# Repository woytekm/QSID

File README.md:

Q-SID: a 4-voice polyphonic MIDI synth based on four SID 8580 chips 

Features:

 Hardware/OS: 

 Q-SID will have a modular construction: every functional block of the device will have it's own PCB:
  - CPU board - Raspberry Pi, or other SoC board with two I2C busses, UART, at least 16 GPIO's, USB and ethernet
  - four voice boards, each with one 8580 SID chip
  - MIDI interface board
  - DSP/mixer board 
  - front controls board with rotary encoders and buttons for sound parameters control 
  - front display board 
  - I2C voltage level converter for voice boards
  - power supply with +9V, +5V switched for CPU, +5V linear for voice boards, +3.3V

 Q-SID will have an operating system in form of single multithreaded process of Linux OS, running on custom Raspbian image scaled down to
 stripped Linux kernel, Q-SID OS process, and prefferably nothing more (to spare CPU cycles and other resources).

 Synthetizer features:

  - 4 SID engines with full SID features
  - polyphonic mode with 4 voice polyphony
  - performance mode with keyboard/voice/patch split 
  - arpeggiator (not sure about exact parameters yet)
  - 2 software LFO's modulating filter cutoff/resonance, PWM, oscillator detune, and other parameters
  - onboard sound effects via internal DSP
  - MIDI in/out with programmable MIDI channel
  - embedded .sid chiptune player

====

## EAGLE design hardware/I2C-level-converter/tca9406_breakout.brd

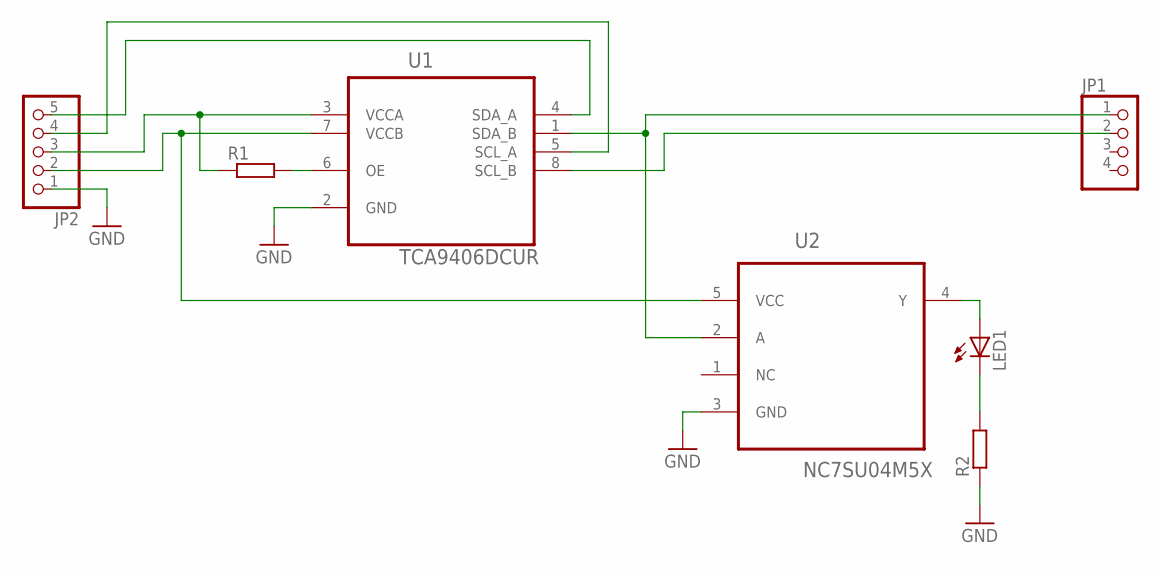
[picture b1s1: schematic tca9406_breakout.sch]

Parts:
JP1: PINHD-1X4; 1X04
JP2: PINHD-1X5; 1X05
LED1: LEDSML1206; SML1206
R1, R2: R-EU_M1406; M1406
U1: TCA9406DCUR; SOP50P310X90-8N
U2: NC7SU04M5X; SOT95P280X145-5N

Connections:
GND: JP2.1, R2.1, U1.2 (GND), U2.3 (GND)
unnamed: JP1.2, U1.8 (SCL_B)
unnamed: JP1.1, U1.1 (SDA_B), U2.2 (A)
unnamed: JP2.5, U1.4 (SDA_A)
unnamed: JP2.4, U1.5 (SCL_A)
unnamed: JP2.3, R1.1, U1.3 (VCCA)
unnamed: JP2.2, U1.7 (VCCB), U2.5 (VCC)
unnamed: LED1.A, U2.4 (Y)
unnamed: R1.2, U1.6 (OE)
unnamed: LED1.C, R2.2

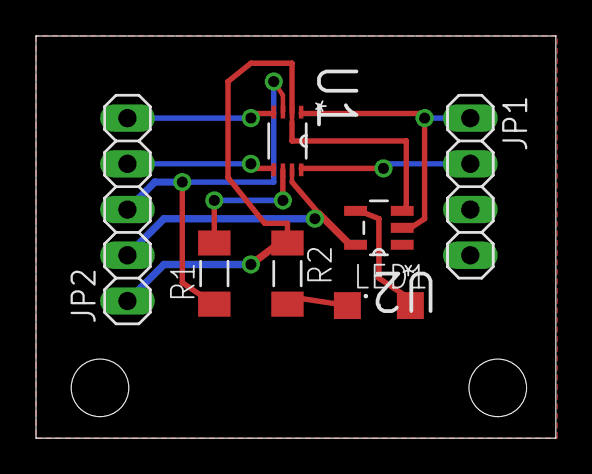
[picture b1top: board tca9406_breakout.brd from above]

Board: 2 copper layers, 28.9 x 22.3 mm, 7 parts (0 on the bottom side), 10 nets.

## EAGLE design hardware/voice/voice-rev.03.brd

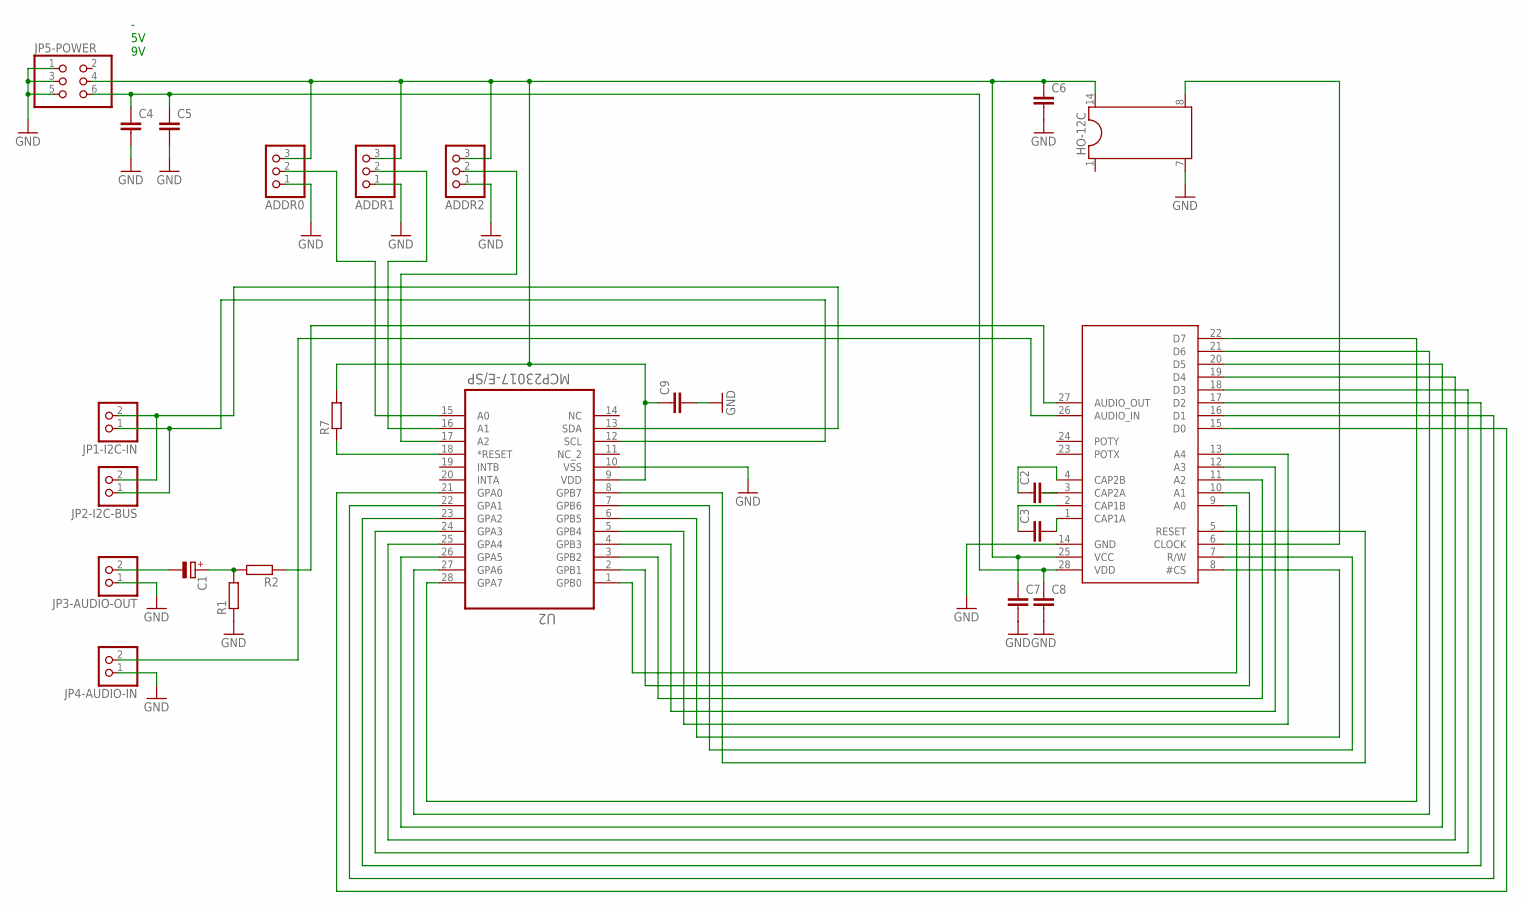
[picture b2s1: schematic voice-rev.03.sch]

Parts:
ADDR0, ADDR1, ADDR2: PINHD-1X3; 1X03
C1: CPOL-EUE2.5-5; E2,5-5
C2, C3: C5/2.5; C5B2.5
C4, C5, C6, C7, C8, C9: C-EU050-024X044; C050-024X044
HO-12C: DIL14/4
JP1-I2C-IN, JP2-I2C-BUS, JP3-AUDIO-OUT, JP4-AUDIO-IN: PINHD-1X2; 1X02
JP5-POWER: PINHD-2X3; 2X03
R1, R2, R7: R-EU_0207/5V; 0207/5V
U2: MCP23017-E/SP; DIP254P762X406-28P
U$1: 6581; DIL28-6

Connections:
GND: ADDR0.1, ADDR1.1, ADDR2.1, C4.2, C5.2, C6.2, C7.2, C8.2, C9.2, HO-12C.7 (8), JP3-AUDIO-OUT.1, JP4-AUDIO-IN.1, JP5-POWER.1, JP5-POWER.3, JP5-POWER.5, R1.1, U2.10 (VSS), U$1.14 (GND)
unnamed: U2.1 (GPB0), U$1.9 (A0)
unnamed: U2.2 (GPB1), U$1.10 (A1)
unnamed: U2.3 (GPB2), U$1.11 (A2)
unnamed: U2.4 (GPB3), U$1.12 (A3)
unnamed: U2.5 (GPB4), U$1.13 (A4)
unnamed: U2.6 (GPB5), U$1.8 (#CS)
unnamed: U2.7 (GPB6), U$1.7 (R/W)
unnamed: U2.8 (GPB7), U$1.5 (RESET)
unnamed: U2.28 (GPA7), U$1.22 (D7)
unnamed: U2.27 (GPA6), U$1.21 (D6)
unnamed: U2.26 (GPA5), U$1.20 (D5)
unnamed: U2.25 (GPA4), U$1.19 (D4)
unnamed: U2.24 (GPA3), U$1.18 (D3)
unnamed: U2.23 (GPA2), U$1.17 (D2)
unnamed: U2.22 (GPA1), U$1.16 (D1)
unnamed: U2.21 (GPA0), U$1.15 (D0)
unnamed: HO-12C.8 (9), U$1.6 (CLOCK)
unnamed: C1.+, R1.2, R2.2
unnamed: C4.1, C5.1, C8.1, JP5-POWER.6, U$1.28 (VDD)
unnamed: R2.1, U$1.27 (AUDIO_OUT)
unnamed: JP4-AUDIO-IN.2, U$1.26 (AUDIO_IN)
unnamed: JP1-I2C-IN.2, JP2-I2C-BUS.2, U2.13 (SDA)
unnamed: JP1-I2C-IN.1, JP2-I2C-BUS.1, U2.12 (SCL)
unnamed: C1.-, JP3-AUDIO-OUT.2
unnamed: C3.2, U$1.1 (CAP1A)
unnamed: C3.1, U$1.2 (CAP1B)
unnamed: C2.2, U$1.3 (CAP2A)
unnamed: C2.1, U$1.4 (CAP2B)
unnamed: ADDR0.2, U2.15 (A0)
unnamed: ADDR1.2, U2.16 (A1)
unnamed: ADDR2.2, U2.17 (A2)
unnamed: R7.1, U2.18 (*RESET)
unnamed: ADDR0.3, ADDR1.3, ADDR2.3, C6.1, C7.1, C9.1, HO-12C.14 (16), JP5-POWER.4, R7.2, U2.9 (VDD), U$1.25 (VCC)

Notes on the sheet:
- 5V 9V

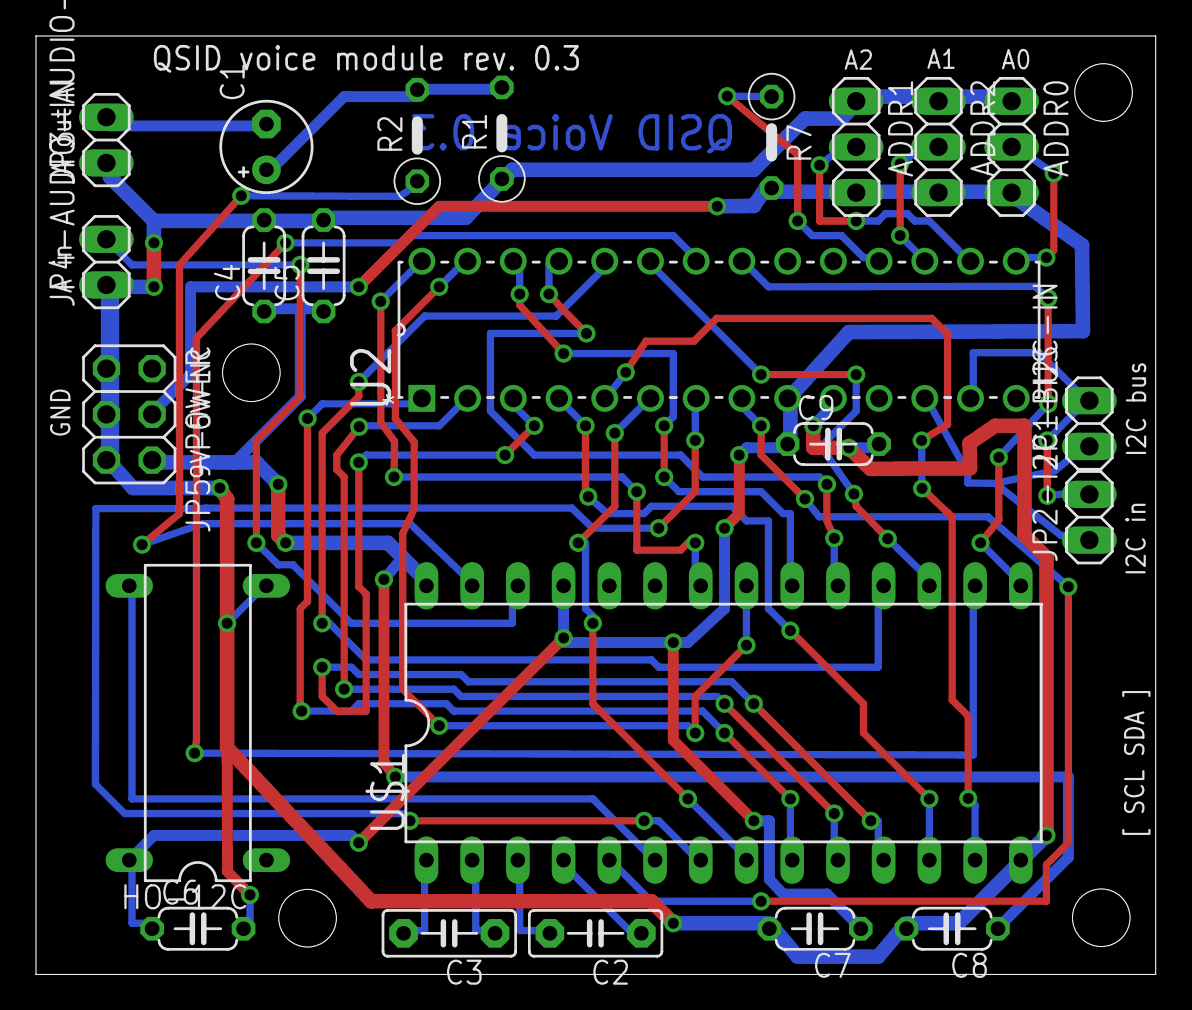
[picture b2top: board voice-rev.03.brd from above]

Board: 2 copper layers, 62.2 x 52.1 mm, 23 parts (0 on the bottom side), 34 nets.

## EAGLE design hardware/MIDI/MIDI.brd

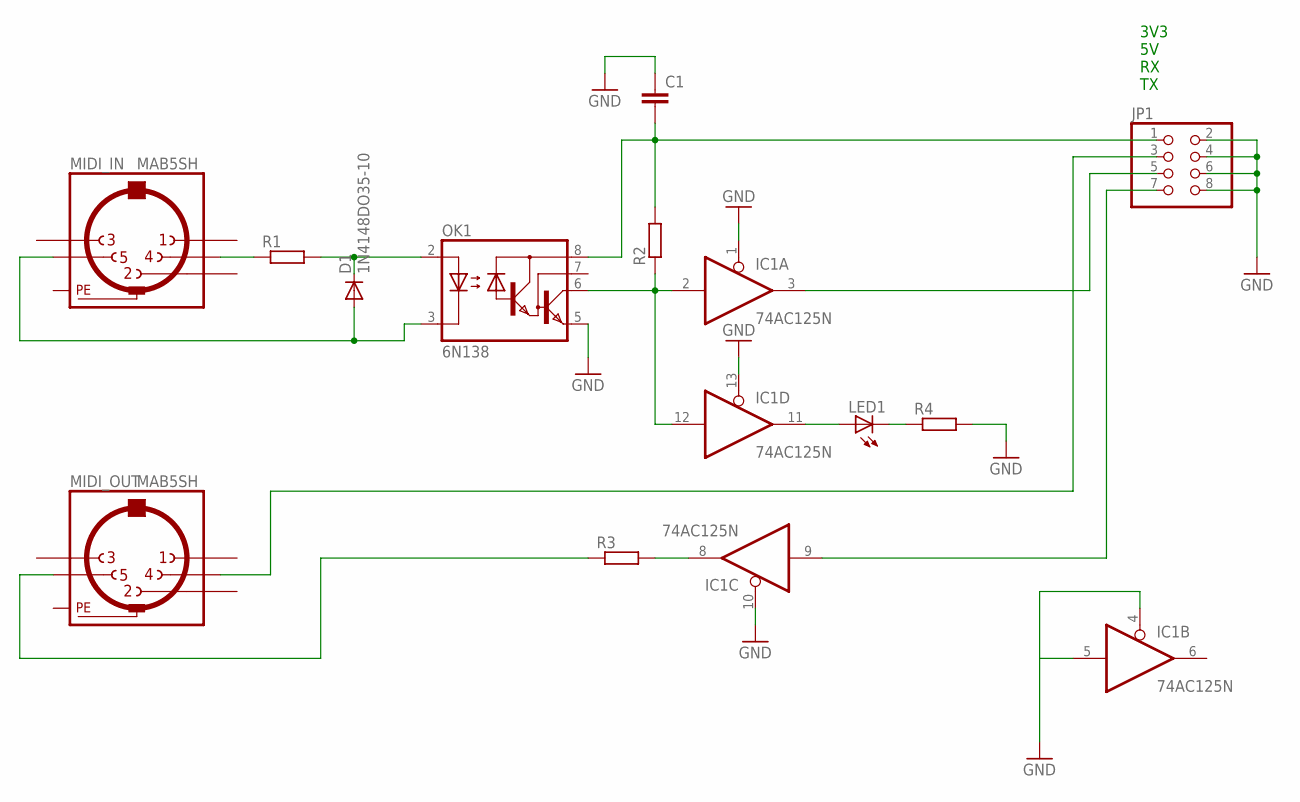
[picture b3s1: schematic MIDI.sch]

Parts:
C1: C-EU050-024X044; C050-024X044
D1: 1N4148DO35-10; DO35-10
IC1: 74AC125N; DIL14
JP1: PINHD-2X4; 2X04
LED1: LED3MM
MIDI_IN: MAB5SH
MIDI_OUT: MAB5SH
OK1: 6N138; DIL08
R1, R2, R3, R4: R-EU_0207/5V; 0207/5V

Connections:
GND: C1.1, IC1.1 (OE), IC1.4 (OE), IC1.5 (I), IC1.7 (GND), IC1.10 (OE), IC1.13 (OE), JP1.2, JP1.4, JP1.6, JP1.8, MIDI_IN.PE, MIDI_IN.PE@ (PE), MIDI_OUT.PE, MIDI_OUT.PE@ (PE), OK1.5 (GND), R4.2
unnamed: MIDI_IN.4, R1.1
unnamed: D1.C, OK1.2 (A), R1.2
unnamed: D1.A, MIDI_IN.5, OK1.3 (C)
unnamed: IC1.8 (O), R3.2
unnamed: IC1.2 (I), IC1.12 (I), OK1.6 (VO), R2.1
unnamed: IC1.3 (O), JP1.5
unnamed: MIDI_OUT.5, R3.1
unnamed: JP1.3, MIDI_OUT.4
unnamed: IC1.9 (I), JP1.7
unnamed: IC1.11 (O), LED1.A
unnamed: LED1.K (C), R4.1
VCC: C1.2, IC1.14 (VCC), JP1.1, OK1.8 (VCC), R2.2

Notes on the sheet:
3V3 5V RX TX

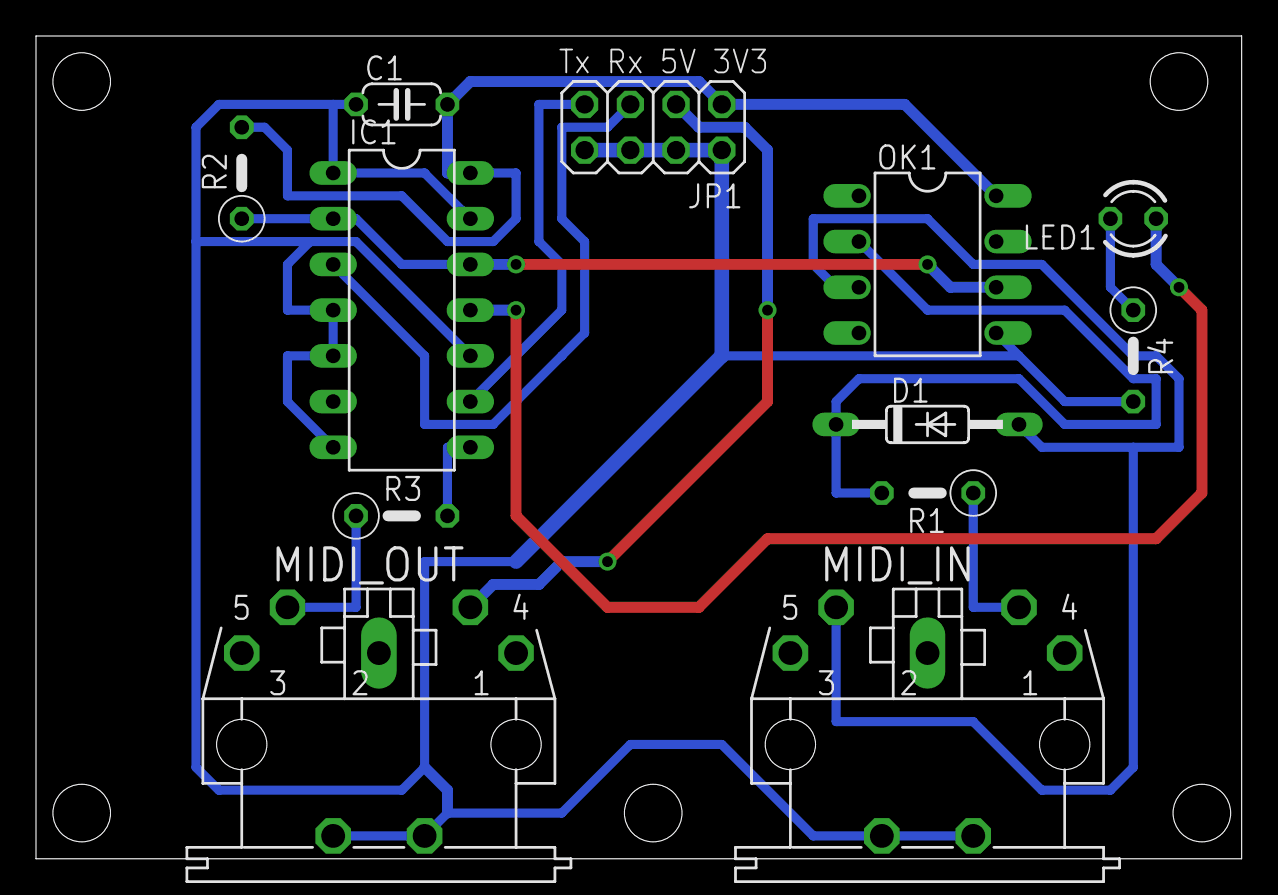
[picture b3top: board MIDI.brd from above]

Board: 2 copper layers, 67.0 x 45.7 mm, 12 parts (0 on the bottom side), 13 nets.

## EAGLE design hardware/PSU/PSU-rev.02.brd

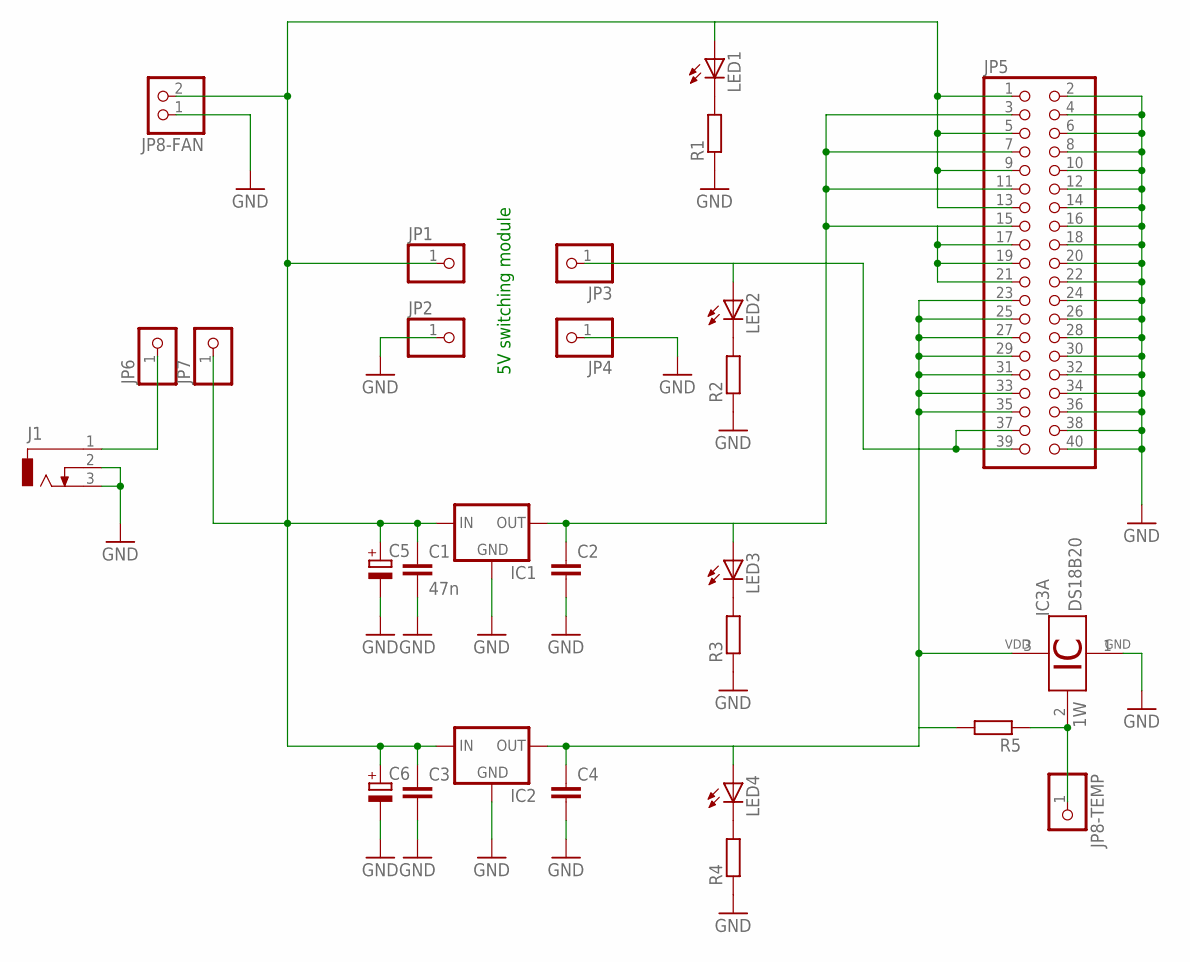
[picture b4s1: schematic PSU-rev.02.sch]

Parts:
C1: 47n; C050-024X044
C2, C3, C4: C-EU050-024X044; C050-024X044
C5, C6: CPOL-EUE3.5-8; E3,5-8
IC1, IC2: 78XXL
IC3: DS18B20; TO92-
J1: DCJ0303
JP1, JP2, JP3, JP4, JP6, JP7, JP8-TEMP: PINHD-1X1; 1X01
JP5: PINHD-2X20; 2X20
JP8-FAN: PINHD-1X2; 1X02
LED1, LED2, LED3, LED4: LEDSML1206; SML1206
R1, R2, R3, R4, R5: R-EU_R1206; R1206

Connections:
GND: C1.2, C2.2, C3.2, C4.2, C5.-, C6.-, IC1.GND, IC2.GND, IC3.1 (GND), J1.2, J1.3, JP2.1, JP4.1, JP5.2, JP5.4, JP5.6, JP5.8, JP5.10, JP5.12, JP5.14, JP5.16, JP5.18, JP5.20, JP5.22, JP5.24, JP5.26, JP5.28, JP5.30, JP5.32, JP5.34, JP5.36, JP5.38, JP5.40, JP8-FAN.1, R1.1, R2.1, R3.1, R4.1
unnamed: C1.1, C3.1, C5.+, C6.+, IC1.IN, IC2.IN, JP1.1, JP5.1, JP5.5, JP5.9, JP5.13, JP7.1, JP8-FAN.2, LED1.A
unnamed: C2.1, IC1.OUT, JP5.3, JP5.7, JP5.11, JP5.15, JP5.17, JP5.19, JP5.21, LED3.A
unnamed: C4.1, IC2.OUT, IC3.3 (VDD), JP5.23, JP5.25, JP5.27, JP5.29, JP5.31, JP5.33, JP5.35, LED4.A, R5.2
unnamed: JP3.1, JP5.37, JP5.39, LED2.A
unnamed: J1.1, JP6.1
unnamed: IC3.2 (1W), JP8-TEMP.1, R5.1
unnamed: LED1.C, R1.2
unnamed: LED2.C, R2.2
unnamed: LED3.C, R3.2
unnamed: LED4.C, R4.2

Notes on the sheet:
5V switching module

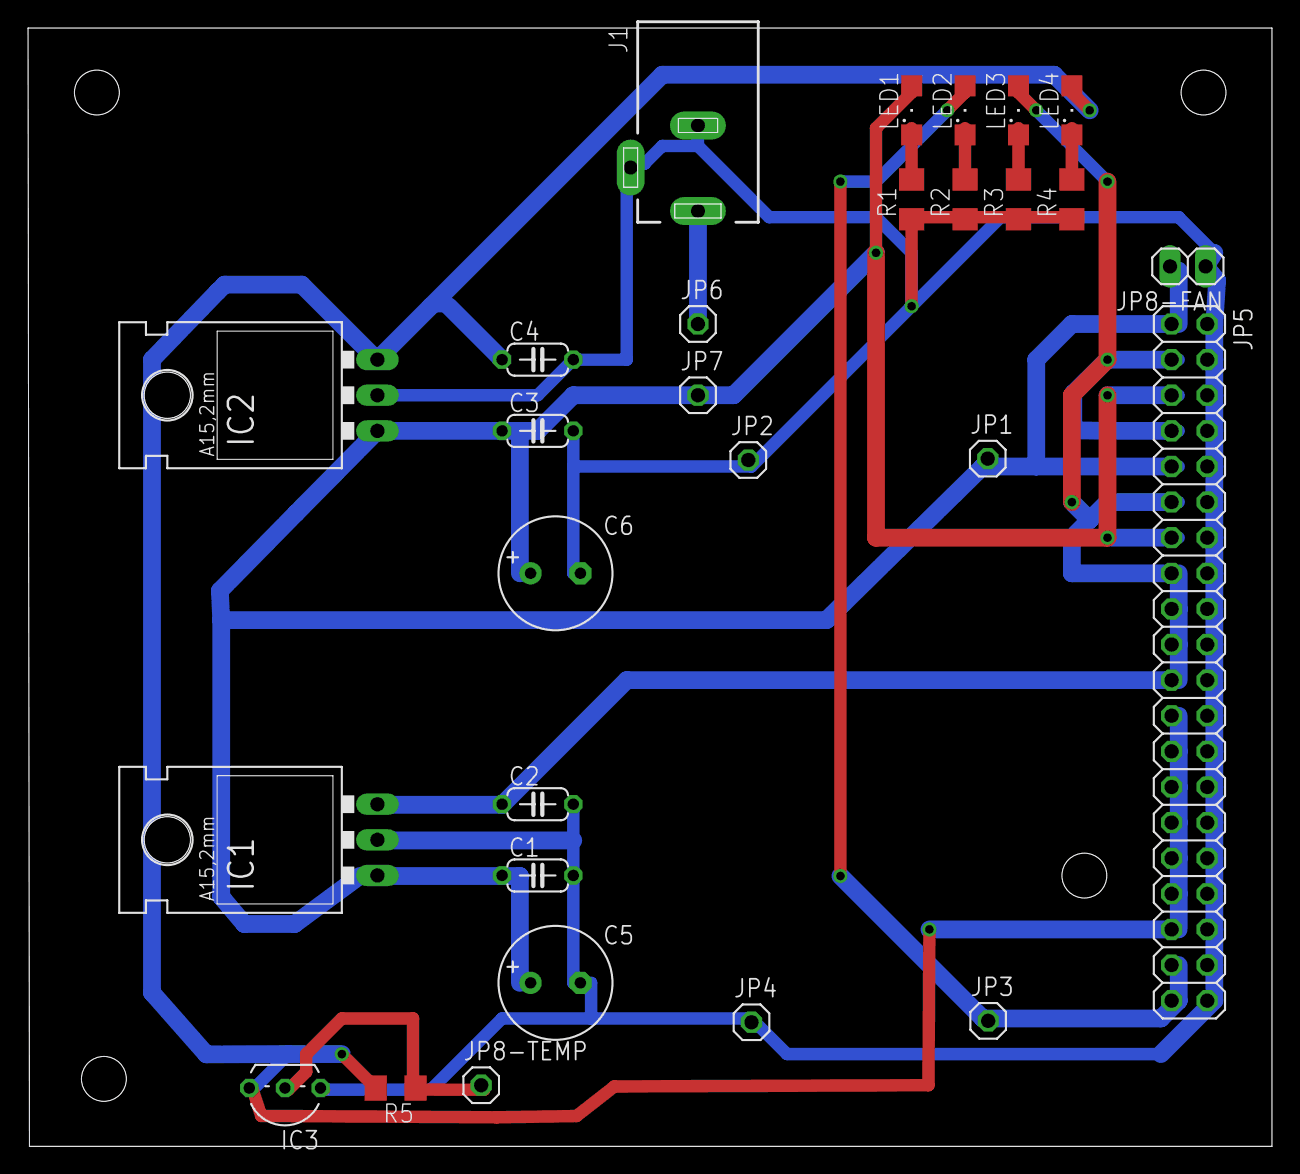
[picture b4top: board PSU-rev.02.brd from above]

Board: 2 copper layers, 88.7 x 79.8 mm, 28 parts (0 on the bottom side), 11 nets.

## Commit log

2014-07-01 README.md
2014-07-04 defining data structures
2014-07-05 preparing subdir tree for OS sources, adding some library code
2014-07-05 base system code
2014-07-13 finished voice autodetection code
2014-07-13 started midi code
2014-07-29 added .sid player code (complete sidplay2 sources modified to use QSID voice board instead of HardSID card)
2014-08-31 added cmdline option allowing to specify Q-SID board address
2014-09-16 added a lot of new stuff: basic polyphony code, midi-in thread, SID writer thread, started SID control code
2014-09-18 started synth patch management
2014-09-24 added parser for midi-in buffer and other minor things
2014-10-02 minor changes in midi receive code
2014-10-02 fixed bug in midi parser code
2014-10-12 optimizations and other minor things
2014-10-12 added some code to test realtime control of SID parameters
2014-10-14 working on test controller
2014-10-17 working on test program
2014-10-21 working on test remote controller, introduced virtual SID registers and other minor stuff
2014-10-26 added oscillator detuning
2014-10-29 added voice stealing
2014-11-04 cleanups, improvements, fixes
2014-11-04 started lfo, other minor improvements
2014-11-05 working on lfo
2014-11-18 added alternative (faster) method of I2C access (BCM2835 library - local, patched copy)
2014-11-23 a lot of changes: started sysex code, rewrote midi receiver, cleanups and cosmetic changes
2014-11-23 fixed small error in midi parser
2014-11-28 working on sysex implementation
2014-11-29 rewrote sysex encoder/decoder
2014-12-22 finished main part of sysex implementation
2014-12-23 added second version of midiump based on qsid midi receive code
2014-12-30 added oscillator silencer feature
2015-01-03 bugfixes and minor improvements
2015-01-07 started patch management
2015-01-08 bugfixes and improvements
2015-01-21 added patch management and started filter adsr generator
